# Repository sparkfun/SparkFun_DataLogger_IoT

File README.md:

SparkFun DataLogger IoT
========================================

[*SparkFun DataLogger IoT (DEV-22462)*](https://www.sparkfun.com/products/22462)

<Basic description of the part.>

Repository Contents
-------------------

<!-- * **/Enclosure** - Enclosure files --> 
* **/Examples** - Test code 
* **/Hardware** - Eagle design files (.brd, .sch)
* **/Production** - Production panel files (.brd)

Documentation
--------------
* **[Hookup Guide](https://docs.sparkfun.com/SparkFun_DataLogger/)** - Basic hookup guide for the DataLogger IoT.
* **[Firmware](https://github.com/sparkfun/SparkFun_DataLogger/)** - Repo for the Datalogger IoT Firmware

Product Versions
----------------
* [DEV-22462](https://www.sparkfun.com/products/22462) - Initial Release

Version History
---------------
* v1.1 - Initial Release

License Information
-------------------

This hardware and the hardware test sketches contained in this GitHub repo are _**open source**_!

Please review the LICENSE.md file for license information. 

If you have any questions or concerns on licensing, please contact technical support on our [SparkFun forums](https://forum.sparkfun.com/viewforum.php?f=152).

Distributed as-is; no warranty is given.

- Your friends at SparkFun.

_<COLLABORATION CREDIT>_

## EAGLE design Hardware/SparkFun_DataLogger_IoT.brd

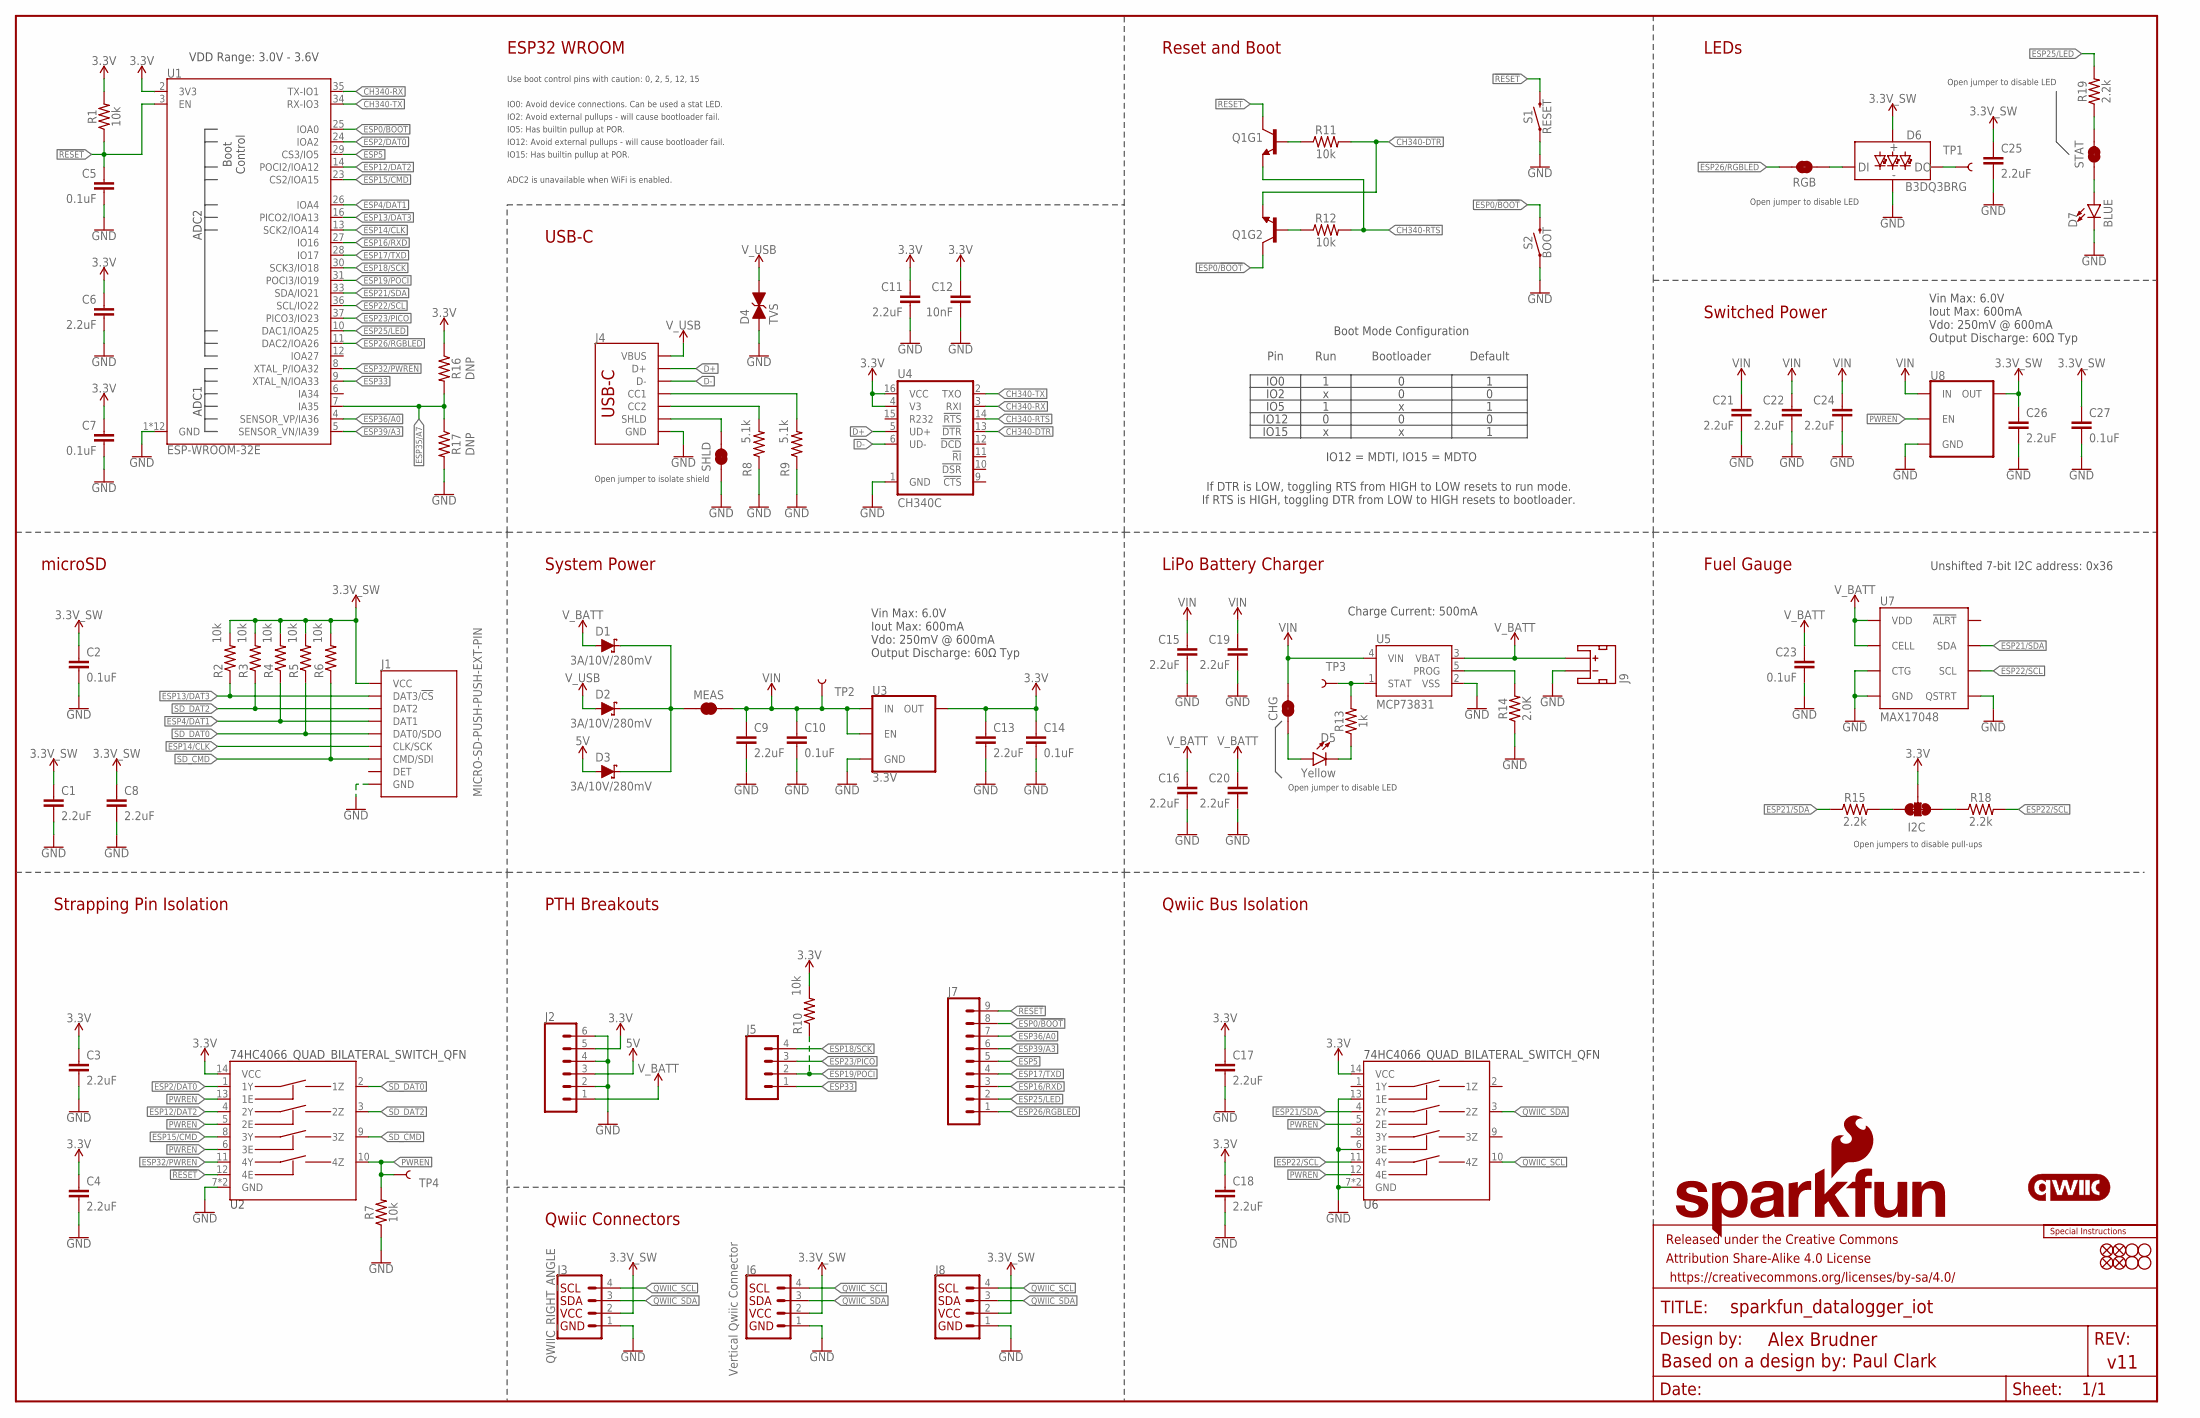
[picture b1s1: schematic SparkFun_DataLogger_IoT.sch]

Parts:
C1, C3, C4, C6, C8, C9, C11, C13, C15, C16, C17, C18, C19, C20, C21, C22, C24, C25, C26: 2.2uF; 0402-TIGHT
C2, C5, C7, C10, C14, C23, C27: 0.1uF; 0402-TIGHT
C12: 10nF; 0402-TIGHT
CHG: JUMPER-SMT_2_NC_TRACE_SILK; SMT-JUMPER_2_NC_TRACE_SILK
D1, D2, D3: 3A/10V/280mV; SOD-323
D4: TVS; 0603
D5: Yellow; LED-0603
D6: B3DQ3BRG
D7: BLUE; LED-0603
FD1, FD2, FD3, FD4: FIDUCIAL1X2; FIDUCIAL-1X2
FRAME1: FRAME-LEDGER; CREATIVE_COMMONS
H1, H2, H3, H4: STAND-OFFTIGHT; STAND-OFF-TIGHT
I2C: JUMPER-SMT_3_2-NC_TRACE_SILK; SMT-JUMPER_3_2-NC_TRACE_SILK
J1: MICRO-SD-PUSH-PUSH-EXT-PIN; MICROSD-EXTERNALPIN
J2: CONN_06NO_SILK_NO_POP; 1X06_NO_SILK
J3: QWIIC_RIGHT_ANGLE; JST04_1MM_RA
J4: USB_C_4-LAYER_PADS; USB-C-16P_4LAYER-PADS
J5: CONN_041X04_NO_SILK_NO_POP; 1X04_NO_SILK
J6: Vertical Qwiic Connector; JST04_1MM_VERT
J7: CONN_09NO_SILK; 1X09_NO_SILK
J8: I2C_STANDARD_NO_SILK; 1X04_NO_SILK
J9: JST_2MM_MALE; JST-2-SMD
LOGO1: SFE_LOGO_NAME.2_INCH; SFE_LOGO_NAME_.2
LOGO2: SFE_LOGO_FLAME.2_INCH; SFE_LOGO_FLAME_.2
LOGO3: SPECIAL_INSTRUCTIONS-ORDERING; ORDERING_INSTRUCTIONS
LOGO4: QWIIC_LOGO_6MM; QWIIC_6MM
MEAS: JUMPER-COMBO_2_NC_TRACE; COMBO-JUMPER_2_NC_TRACE
Q1: TRANS_NPN_DUAL-MBT3904DW1T1; SC70-6
R1, R2, R3, R4, R5, R6, R7, R10, R11, R12: 10k; 0402-TIGHT
R8, R9: 5.1k; 0402-TIGHT
R13: 1k; 0402-TIGHT
R14: 2.0K; 0402-TIGHT
R15, R18, R19: 2.2k; 0402-TIGHT
R16, R17: DNP; 0402-TIGHT_NO_CREAM
RGB: JUMPER-SMT_2_NC_TRACE_SILK; SMT-JUMPER_2_NC_TRACE_SILK
S1: RESET; TACTILE_SWITCH_SMD_RIGHT_ANGLE
S2: BOOT; TACTILE_SWITCH_SMD_RIGHT_ANGLE
SHLD: JUMPER-SMT_2_NC_TRACE_SILK; SMT-JUMPER_2_NC_TRACE_SILK
STAT: JUMPER-SMT_2_NC_TRACE_SILK; SMT-JUMPER_2_NC_TRACE_SILK
TP1, TP2, TP3, TP4: TEST-POINT3X5; PAD.03X.05
U1: ESP-WROOM-32E; ESP-WROOM-32D-NARROW
U2, U6: 74HC4066_QUAD_BILATERAL_SWITCH_QFN; 14-QFN
U3, U8: 3.3V; SOT23-5
U4: CH340C; SO016
U5: MCP73831; SOT23-5
U7: MAX17048; DFN-8

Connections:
3.3V: C3.1, C4.1, C6.1, C7.1, C11.1, C12.1, C13.1, C14.1, C17.1, C18.1, I2C.2, J2.5, R1.2, R10.2, R16.1, U1.2 (3V3), U2.14 (VCC), U3.5 (OUT), U4.4 (V3), U4.16 (VCC), U6.14 (VCC)
3.3V_SW: C1.1, C2.1, C8.1, C25.1, C26.1, C27.1, D6.2 (VCC), J1.4 (VCC), J3.2, J6.2, J8.2, R2.2, R3.2, R4.2, R5.2, R6.2, U8.5 (OUT)
5V: D3.A, J2.3
!RESET!: C5.1, J7.9, Q1.3 (C), R1.1, S1.2, U1.3 (EN), U2.12 (4E)
CH340-DTR: Q1.1 (E), R11.2, U4.13 (!DTR)
CH340-RTS: Q1.4 (E), R12.2, U4.14 (!RTS)
CH340-RX: U1.35 (TX-IO1), U4.3 (RXI)
CH340-TX: U1.34 (RX-IO3), U4.2 (TXO)
D+: J4.A6 (D+), J4.B6 (D+), U4.5 (UD+)
D-: J4.A7 (D-), J4.B7 (D-), U4.6 (UD-)
ESP0/!BOOT!: J7.8, Q1.6 (C), S2.2, U1.25 (IOA0)
ESP2/DAT0: U1.24 (IOA2), U2.1 (1Y)
ESP4/DAT1: J1.8 (DAT1), R4.1, U1.26 (IOA4)
ESP5: J7.5, U1.29 (CS3/IO5)
ESP12/DAT2: U1.14 (POCI2/IOA12), U2.4 (2Y)
ESP13/DAT3: J1.2 (DAT3/!CS!), R2.1, U1.16 (PICO2/IOA13)
ESP14/CLK: J1.5 (CLK/SCK), U1.13 (SCK2/IOA14)
ESP15/CMD: U1.23 (CS2/IOA15), U2.8 (3Y)
ESP16/RXD: J7.3, U1.27 (IO16)
ESP17/TXD: J7.4, U1.28 (IO17)
ESP18/SCK: J5.4, U1.30 (SCK3/IO18)
ESP19/POCI: J5.2, R10.1, U1.31 (POCI3/IO19)
ESP21/SDA: R15.1, U1.33 (SDA/IO21), U6.4 (2Y), U7.8 (SDA)
ESP22/SCL: R18.2, U1.36 (SCL/IO22), U6.11 (4Y), U7.7 (SCL)
ESP23/PICO: J5.3, U1.37 (PICO3/IO23)
ESP25/LED: J7.2, R19.2, U1.10 (DAC1/IOA25)
ESP26/RGBLED: J7.1, RGB.2, U1.11 (DAC2/IOA26)
ESP32/PWREN: U1.8 (XTAL_P/IOA32), U2.11 (4Y)
ESP33: J5.1, U1.9 (XTAL_N/IOA33)
ESP35/A7: R16.2, R17.1, U1.7 (IA35)
ESP36/A0: J7.7, U1.4 (SENSOR_VP/IA36)
ESP39/A3: J7.6, U1.5 (SENSOR_VN/IA39)
GND: C1.2, C2.2, C3.2, C4.2, C5.2, C6.2, C7.2, C8.2, C9.2, C10.2, C11.2, C12.2, C13.2, C14.2, C15.2, C16.2, C17.2, C18.2, C19.2, C20.2, C21.2, C22.2, C23.2, C24.2, C25.2, C26.2, C27.2, D4.1 (A), D6.1 (GND), D7.C, J1.6 (GND), J1.10 (GND), J1.11 (GND), J1.12 (GND), J1.13 (GND), J2.2, J2.4, J2.6, J3.1, J4.GND, J4.GND2 (GND), J6.1, J8.1, J9.1 (-), R7.1, R8.1, R9.1, R14.1, R17.2, S1.1, S2.1, SHLD.1, U1.1 (GND), U1.15 (GND), U1.38 (GND), U1.GND1 (GND), U1.GNDT1 (GND), U1.GNDT2 (GND), U1.GNDT3 (GND), U1.GNDT4 (GND), U1.GNDT5 (GND), U1.GNDT6 (GND), U1.GNDT7 (GND), U1.GNDT8 (GND), U2.7 (GND), U2.EPAD (GND), U3.2 (GND), U4.1 (GND), U5.2 (VSS), U6.6 (3E), U6.7 (GND), U6.13 (1E), U6.EPAD (GND), U7.1 (CTG), U7.4 (GND), U7.6 (QSTRT), U7.9 (GND), U8.2 (GND)
unnamed: J4.B5 (CC2), R8.2
unnamed: J4.A5 (CC1), R9.2
unnamed: D1.C, D2.C, D3.C, MEAS.1, MEAS.3 (1)
unnamed: Q1.2 (B), R12.1
unnamed: Q1.5 (B), R11.1
unnamed: R19.1, STAT.2
unnamed: D6.4 (DO), TP1.1
unnamed: CHG.1, D5.A
unnamed: D5.C, R13.1
unnamed: R13.2, TP3.1, U5.1 (STAT)
unnamed: R14.2, U5.5 (PROG)
unnamed: D6.3 (DI), RGB.1
unnamed: D7.A, STAT.1
unnamed: I2C.1, R18.1
unnamed: I2C.3, R15.2
PWREN: R7.2, TP4.1, U2.5 (2E), U2.6 (3E), U2.10 (4Z), U2.13 (1E), U6.5 (2E), U6.12 (4E), U8.3 (EN)
QWIIC_SCL: J3.4, J6.4, J8.4, U6.10 (4Z)
QWIIC_SDA: J3.3, J6.3, J8.3, U6.3 (2Z)
SD_CMD: J1.3 (CMD/SDI), R6.1, U2.9 (3Z)
SD_DAT0: J1.7 (DAT0/SDO), R5.1, U2.2 (1Z)
SD_DAT2: J1.1 (DAT2), R3.1, U2.3 (2Z)
SHIELD: J4.SHLD1 (SHLD), J4.SHLD2 (SHLD), J4.SHLD3 (SHLD), J4.SHLD4 (SHLD), SHLD.2
VIN: C9.1, C10.1, C15.1, C19.1, C21.1, C22.1, C24.1, CHG.2, MEAS.2, MEAS.4 (2), TP2.1, U3.1 (IN), U3.3 (EN), U5.4 (VIN), U8.1 (IN)
V_BATT: C16.1, C20.1, C23.1, D1.A, J2.1, J9.2 (+), U5.3 (VBAT), U7.2 (CELL), U7.3 (VDD)
V_USB: D2.A, D4.2 (C), J4.VBUS1 (VBUS), J4.VBUS2 (VBUS)

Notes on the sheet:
ESP32 WROOM
USB-C
Reset and Boot
LEDs
Switched Power
Fuel Gauge
LiPo Battery Charger
System Power
microSD
Strapping Pin Isolation
Qwiic Bus Isolation
PTH Breakouts
Charge Current: 500mA
VDD Range: 3.0V - 3.6V
Vin Max: 6.0V Iout Max: 600mA Vdo: 250mV @ 600mA Output Discharge: 60Ω Typ
If DTR is LOW, toggling RTS from HIGH to LOW resets to run mode. If RTS is HIGH, toggling DTR from LOW to HIGH resets to bootloader.
Pin
IO0
IO2
IO12
IO15
IO5
Run
Bootloader
Default
IO12 = MDTI, IO15 = MDTO
Boot Mode Configuration
IO0: Avoid device connections. Can be used a stat LED.
ADC2 is unavailable when WiFi is enabled.
IO12: Avoid external pullups - will cause bootloader fail.
Use boot control pins with caution: 0, 2, 5, 12, 15
IO2: Avoid external pullups - will cause bootloader fail.
IO15: Has builtin pullup at POR.
IO5: Has builtin pullup at POR.
Open jumpers to disable pull-ups
Open jumper to disable LED
Open jumper to isolate shield
Based on a design by: Paul Clark
Qwiic Connectors
TP2

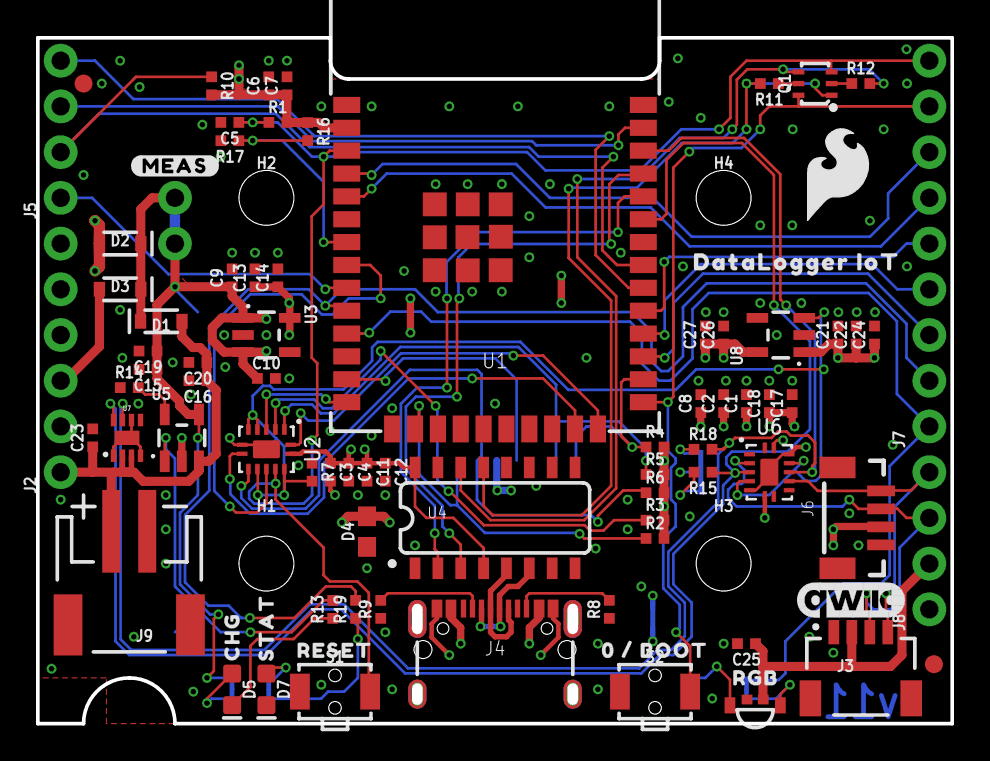
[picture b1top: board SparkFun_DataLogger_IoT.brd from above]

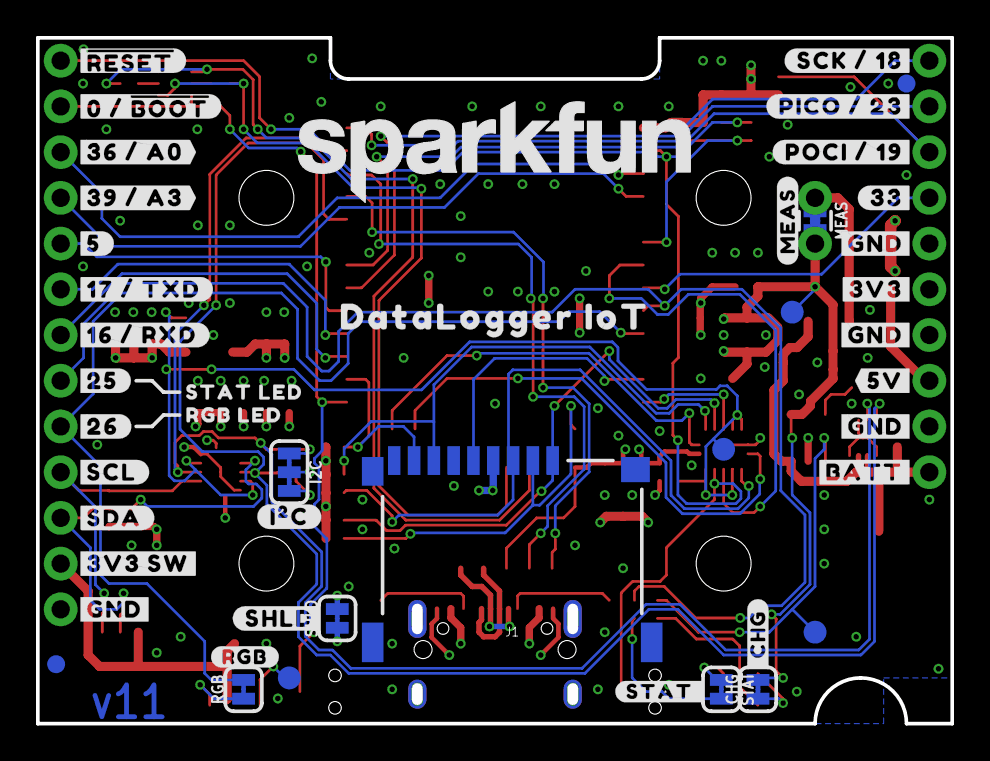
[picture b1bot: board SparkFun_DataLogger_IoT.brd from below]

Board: 4 copper layers, 50.4 x 37.7 mm, 136 parts (47 on the bottom side), 58 nets.

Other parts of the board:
U$1: DATALOGGER_IOT5
U$2: RESET0
U$3: STAT0
U$4: CHG0
U$5: #STAT_#0
U$6: #RGB#0
U$7: 0_#_BOOT0
U$8: #_CHG#0
U$9, U$10: #MEAS#0
U$11: RGB0
U$12: #5#0
U$13: SFE_LOGO_FLAME_STOP_.1
U$14: DATALOGGER_IOT2
U$16: ##RESET##0
U$17: #0_#_#BOOT##0
U$18: #36_#_A0#0
U$19: #39_#_A3#0
U$21: #17_#_TXD#0
U$22: #16_#_RXD#0
U$23: #25#0
U$24: #26#0
U$25: #SCL#0
U$26: #SDA#0
U$27: #3V3_SW#0
U$28: #GND#0
U$29, U$30, U$31: #GND#1
U$32: #BATT#0
U$33: #5V#0
U$34: #3V3#0
U$35: #33#0
U$36: #POCI_#_19#0
U$37: #PICO_#_23#0
U$38: #SCK_#_18#0
U$45: #SHLD#0
U$46: #I�C#0
U$47: STAT_LED0
U$48: RGB_LED0

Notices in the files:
parts and their libraries:
SparkFun-Capacitors: Licensing: Creative Commons ShareAlike 4.0 International - https://creativecommons.org/licenses/by-sa/4.0
SparkFun-Aesthetics: Released under the Creative Commons Attribution Share-Alike 4.0 License
SparkFun-Aesthetics: https://creativecommons.org/licenses/by-sa/4.0
